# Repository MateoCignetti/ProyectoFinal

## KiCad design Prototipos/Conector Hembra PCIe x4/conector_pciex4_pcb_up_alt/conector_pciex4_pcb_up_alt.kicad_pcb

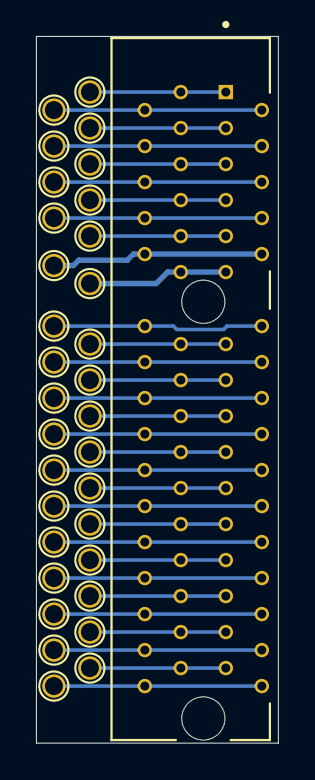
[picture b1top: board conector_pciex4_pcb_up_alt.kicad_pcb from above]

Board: 2 copper layers, 13.4 x 39.3 mm, 33 parts (0 on the bottom side), 27 nets.

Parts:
J1: 10018783-10211TLF; AMPHENOL_PCIe-x4_10018783-10211TLF
TP1: HP_Power; TestPoint_THTPad_D1.5mm_Drill0.7mm
TP2, TP3, TP4, TP5: PGND; TestPoint_THTPad_D1.5mm_Drill0.7mm
TP6: 5Vdc; TestPoint_THTPad_D1.5mm_Drill0.7mm
TP7, TP8, TP9: 12Vdc; TestPoint_THTPad_D1.5mm_Drill0.7mm
TP10: 48Vac_L; TestPoint_THTPad_D1.5mm_Drill0.7mm
TP11: 48Vac_N; TestPoint_THTPad_D1.5mm_Drill0.7mm
TP12, TP31: AGND; TestPoint_THTPad_D1.5mm_Drill0.7mm
TP13: 3,3Vdc_Signal; TestPoint_THTPad_D1.5mm_Drill0.7mm
TP14: S1; TestPoint_THTPad_D1.5mm_Drill0.7mm
TP15: S2; TestPoint_THTPad_D1.5mm_Drill0.7mm
TP16: S3; TestPoint_THTPad_D1.5mm_Drill0.7mm
TP17: S4; TestPoint_THTPad_D1.5mm_Drill0.7mm
TP18: S5; TestPoint_THTPad_D1.5mm_Drill0.7mm
TP19: S6; TestPoint_THTPad_D1.5mm_Drill0.7mm
TP20: S7; TestPoint_THTPad_D1.5mm_Drill0.7mm
TP21: S8; TestPoint_THTPad_D1.5mm_Drill0.7mm
TP22: S9; TestPoint_THTPad_D1.5mm_Drill0.7mm
TP23: S10; TestPoint_THTPad_D1.5mm_Drill0.7mm
TP24: S11; TestPoint_THTPad_D1.5mm_Drill0.7mm
TP25: S12; TestPoint_THTPad_D1.5mm_Drill0.7mm
TP26: S13; TestPoint_THTPad_D1.5mm_Drill0.7mm
TP27: S14; TestPoint_THTPad_D1.5mm_Drill0.7mm
TP28: S15; TestPoint_THTPad_D1.5mm_Drill0.7mm
TP29: S16; TestPoint_THTPad_D1.5mm_Drill0.7mm
TP30: MODULE_IDENT; TestPoint_THTPad_D1.5mm_Drill0.7mm
TP32: HP_Signal; TestPoint_THTPad_D1.5mm_Drill0.7mm

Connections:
unnamed: J1.A1, J1.B1, TP1.1
unnamed: J1.A2, J1.A3, J1.A4, J1.A5, J1.B2, J1.B3, J1.B4, J1.B5, TP2.1, TP3.1, TP4.1, TP5.1
unnamed: J1.A6, J1.B6, TP6.1
unnamed: J1.A7, J1.A8, J1.A9, J1.B7, J1.B8, J1.B9, TP7.1, TP8.1, TP9.1
unnamed: J1.A10, J1.B10, TP10.1
unnamed: J1.A11, J1.B11, TP11.1
unnamed: J1.A12, J1.B12, TP12.1
unnamed: J1.A13, J1.B13, TP13.1
unnamed: J1.A14, J1.B14, TP14.1
unnamed: J1.A15, J1.B15, TP15.1
unnamed: J1.A16, J1.B16, TP16.1
unnamed: J1.A17, J1.B17, TP17.1
unnamed: J1.A18, J1.B18, TP18.1
unnamed: J1.A19, J1.B19, TP19.1
unnamed: J1.A20, J1.B20, TP20.1
unnamed: J1.A21, J1.B21, TP21.1
unnamed: J1.A22, J1.B22, TP22.1
unnamed: J1.A23, J1.B23, TP23.1
unnamed: J1.A24, J1.B24, TP24.1
unnamed: J1.A25, J1.B25, TP25.1
unnamed: J1.A26, J1.B26, TP26.1
unnamed: J1.A27, J1.B27, TP27.1
unnamed: J1.A28, J1.B28, TP28.1
unnamed: J1.A29, J1.B29, TP29.1
unnamed: J1.A30, J1.B30, TP30.1
unnamed: J1.A31, J1.B31, TP31.1
unnamed: J1.A32, J1.B32, TP32.1

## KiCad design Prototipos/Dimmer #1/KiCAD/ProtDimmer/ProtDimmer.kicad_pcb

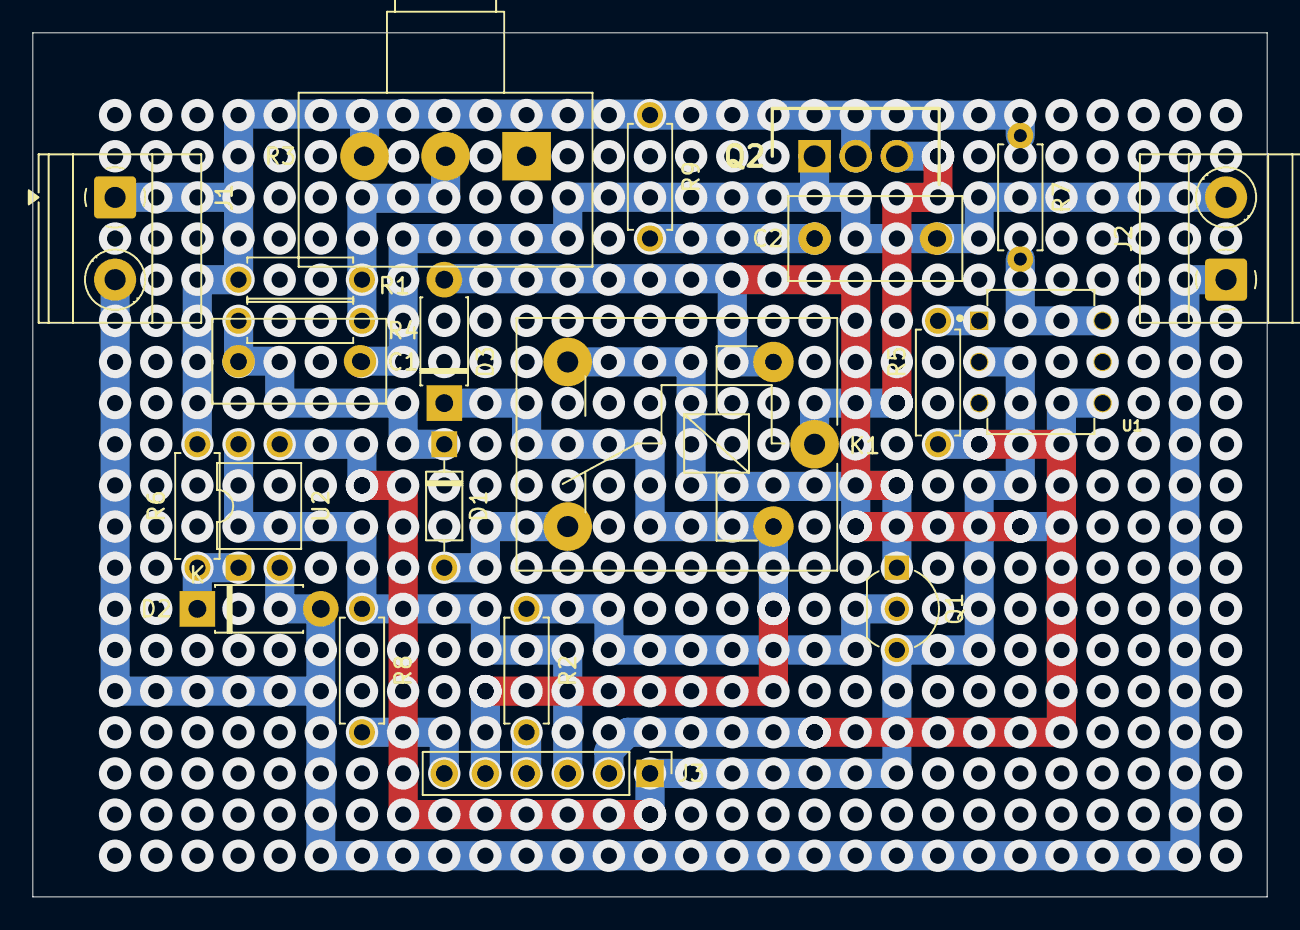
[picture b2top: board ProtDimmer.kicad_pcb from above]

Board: 2 copper layers, 76.2 x 53.3 mm, 22 parts (0 on the bottom side), 20 nets.

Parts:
C1: 100nF; C_Disc_D10.5mm_W5.0mm_P7.50mm
C2: 10nF; C_Disc_D10.5mm_W5.0mm_P7.50mm
D1: DB3; D_DO-35_SOD27_P7.62mm_Horizontal
D2, D3: D_Small; D_DO-41_SOD81_P7.62mm_Horizontal
J1, J2: Conn_01x02; TerminalBlock_Phoenix_MKDS-1,5-2-5.08_1x02_P5.08mm_Horizont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
J3: Conn_01x05; PinHeader_1x06_P2.54mm_Vertical
K1: SRD-05VDC-SL-C; Relay_SPDT_SANYOU_SRD_Series_Form_C
Q1: BC548B; TO-92_Inline_Wide
Q2: BT137; TO254P470X1000X2000-3P
R1: 150k; R_Axial_DIN0207_L6.3mm_D2.5mm_P7.62mm_Horizontal
R2: 12k; R_Axial_DIN0207_L6.3mm_D2.5mm_P7.62mm_Horizontal
R3: 100k; Potentiometer_Alps_RK163_Single_Horizontal
R4: 1k; R_Axial_DIN0207_L6.3mm_D2.5mm_P7.62mm_Horizontal
R5, R7: 82; R_Axial_DIN0207_L6.3mm_D2.5mm_P7.62mm_Horizontal
R6: 1.8k; R_Axial_DIN0207_L6.3mm_D2.5mm_P7.62mm_Horizontal
R8: 10k; R_Axial_DIN0207_L6.3mm_D2.5mm_P7.62mm_Horizontal
R9: 51; R_Axial_DIN0207_L6.3mm_D2.5mm_P7.62mm_Horizontal
U1: MOC3021M; DIP762W45P254L889H508Q6
U2: EL817; DIP-4_W7.62mm

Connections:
3.3Vcc: J3.6, R8.1
5Vcc: D3.1 (K), J3.5, K1.5
48Vca_L: J1.1, Q2.2 (MT2), R1.1, R3.3, R6.1, R7.1, R9.1
48Vca_N: D2.2 (A), J1.2, J2.1, U2.2
GND: J3.1, Q1.3 (E), U1.2, U2.3
LOAD_L: C1.2, C2.2, J2.2, Q2.1 (MT1)
unnamed: C2.1, R9.2
unnamed: D1.2 (A), K1.4
unnamed: C1.1, D1.1 (K), R4.2
unnamed: D2.1 (K), R6.2, U2.1
unnamed: K1.3, U1.4
unnamed: Q1.2 (B), R2.2
unnamed: K1.1, Q2.3 (G)
unnamed: R1.2, R3.2, R4.1
unnamed: R5.2, U1.1
unnamed: R7.2, U1.6
RELAY_T2: D3.2 (A), K1.2, Q1.1 (C)
UC_DOUT: J3.2, R5.1
UC_PHASE: J3.3, R8.2, U2.4
UC_RELAY: J3.4, R2.1

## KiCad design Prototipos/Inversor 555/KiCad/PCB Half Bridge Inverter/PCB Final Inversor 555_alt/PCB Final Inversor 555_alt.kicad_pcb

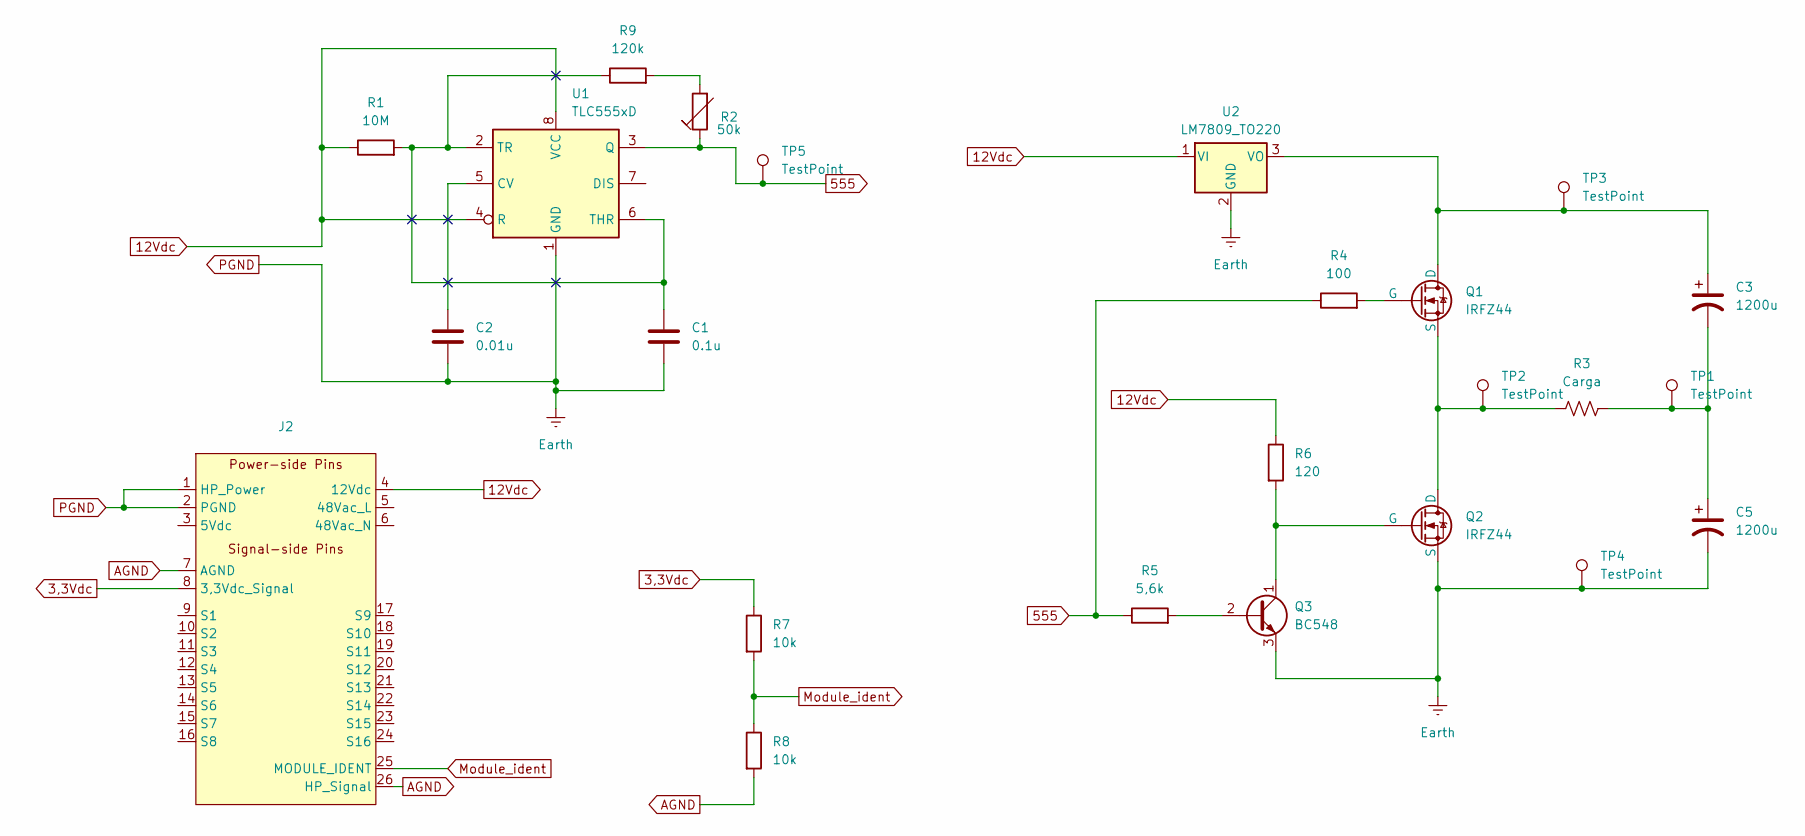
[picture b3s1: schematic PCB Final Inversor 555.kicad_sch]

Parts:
C1: 0.1u; C_Disc_D3.8mm_W2.6mm_P2.50mm
C2: 0.01u; C_Disc_D3.8mm_W2.6mm_P2.50mm
C3, C5: 1200u; C_Radial_D10.0mm_H16.0mm_P5.00mm
J2: BUS_PCIE_x4_NSH
Q1, Q2: IRFZ44; TO-220-3_Horizontal_TabDown
Q3: BC548; TO-92_Inline_Wide
R1: 10M; R_Axial_DIN0207_L6.3mm_D2.5mm_P7.62mm_Horizontal
R2: 50k; Potentiometer_Alps_RK09K_Single_Vertical
R3: Carga; R_Axial_DIN0207_L6.3mm_D2.5mm_P7.62mm_Horizontal
R4: 100; R_Axial_DIN0207_L6.3mm_D2.5mm_P7.62mm_Horizontal
R5: 5,6k; R_Axial_DIN0207_L6.3mm_D2.5mm_P7.62mm_Horizontal
R6: 120; R_Axial_DIN0207_L6.3mm_D2.5mm_P7.62mm_Horizontal
R7, R8: 10k; R_Axial_DIN0207_L6.3mm_D2.5mm_P7.62mm_Horizontal
R9: 120k; R_Axial_DIN0207_L6.3mm_D2.5mm_P7.62mm_Horizontal
TP1, TP2, TP3, TP4, TP5: TestPoint; TestPoint_Loop_D1.80mm_Drill1.0mm_Beaded
U1: TLC555xD; DIP-8_W10.16mm
U2: LM7809_TO220; TO-220-3_Horizontal_TabDown

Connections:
3,3Vdc: J2.8 (3,3Vdc_Signal), R7.1
12Vdc: J2.4 (12Vdc), R1.1, R6.1, U1.4 (R), U1.8 (VCC), U2.1 (VI)
555: R2.1, R4.1, R5.1, TP5.1, U1.3 (Q)
AGND: J2.7 (AGND), J2.26 (HP_Signal), R8.2
Module_ident: J2.25 (MODULE_IDENT), R7.2, R8.1
unnamed: C3.2, C5.1, R3.2, TP1.1
unnamed: C3.1, Q1.1 (D), TP3.1, U2.3 (VO)
unnamed: Q1.2 (G), R4.2
unnamed: Q1.3 (S), Q2.1 (D), R3.1, TP2.1
unnamed: Q2.2 (G), Q3.1 (C), R6.2
unnamed: Q3.2 (B), R5.2
unnamed: R2.2, R2.3, R9.2
unnamed: C2.1, U1.5 (CV)
unnamed: C1.1, R1.2, R9.1, U1.2 (TR), U1.6 (THR)
PGND: C1.2, C2.2, C5.2, J2.1 (HP_Power), J2.2 (PGND), Q2.3 (S), Q3.3 (E), TP4.1, U1.1 (GND), U2.2 (GND)

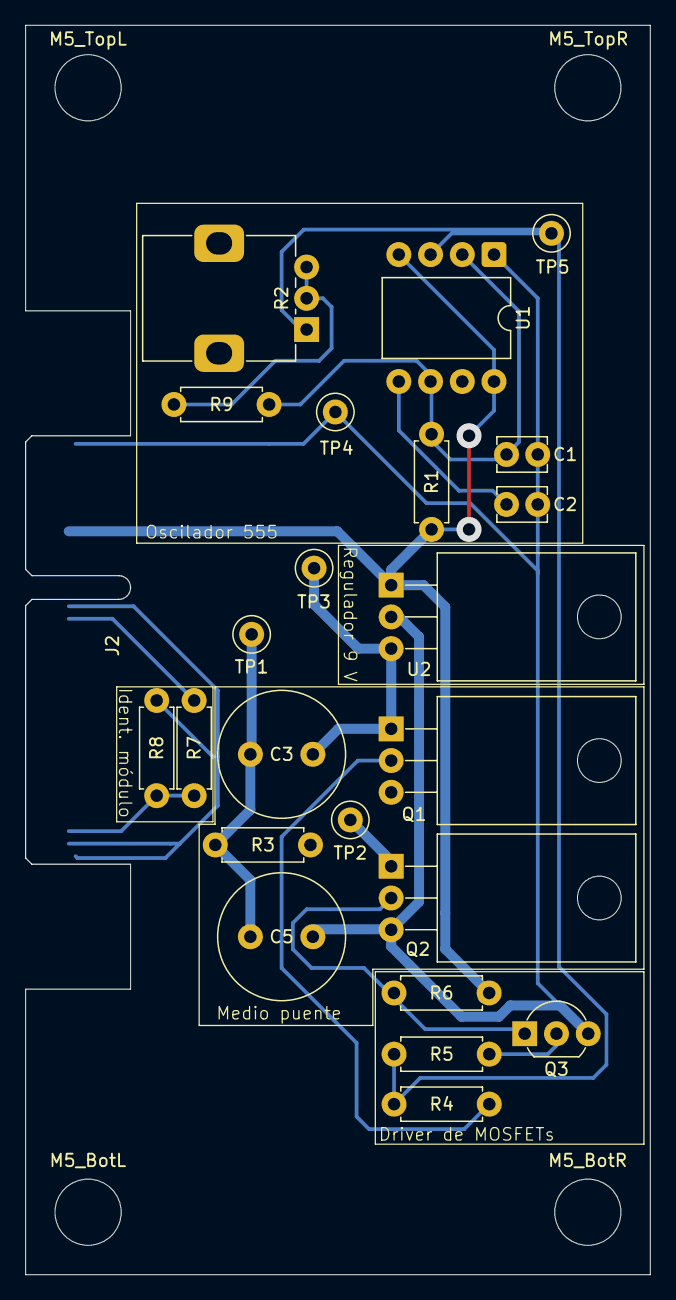
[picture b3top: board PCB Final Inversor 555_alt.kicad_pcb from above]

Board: 2 copper layers, 50.0 x 100.0 mm, 28 parts (0 on the bottom side), 15 nets.

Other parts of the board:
M5_BotL, M5_BotR, M5_TopL, M5_TopR: MountingHole_5.3mm_M5
